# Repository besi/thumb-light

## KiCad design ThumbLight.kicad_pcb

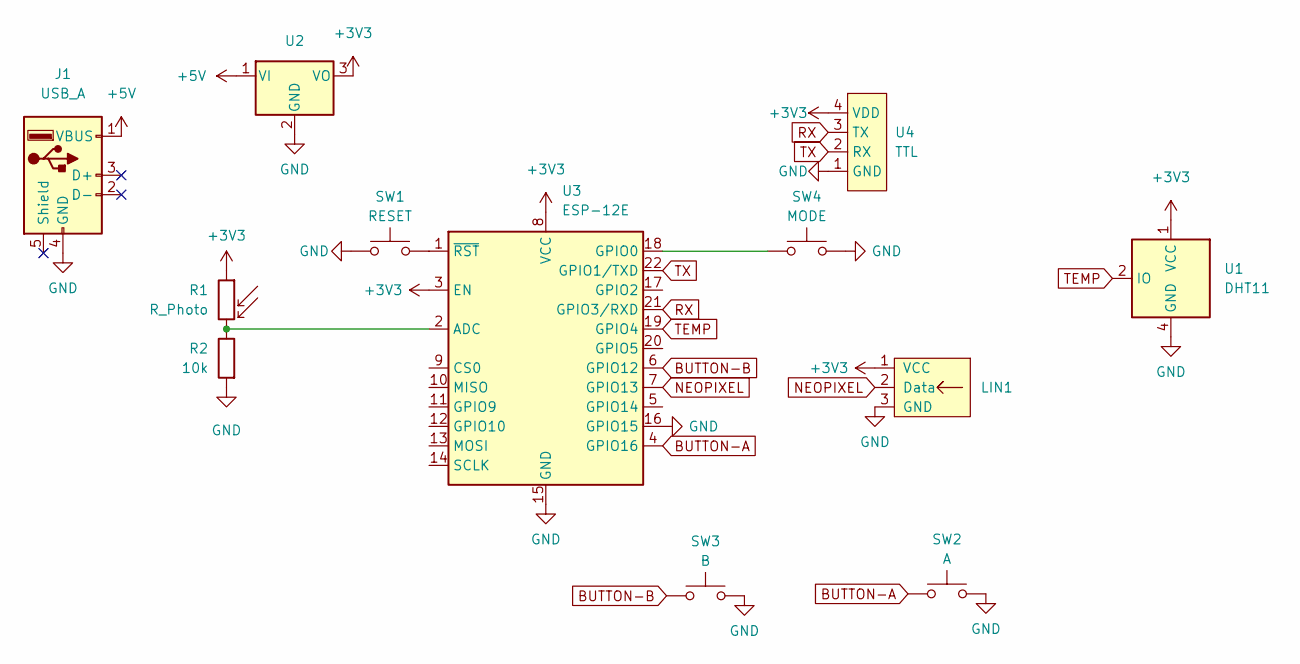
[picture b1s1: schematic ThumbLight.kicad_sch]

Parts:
J1: USB_A; usb-a-pcb
LIN1: LEDs_In; neopixel-strip
R1: R_Photo; R_LDR_5.0x4.1mm_P3mm_Vertical
R2: 10k; R_Axial_DIN0207_L6.3mm_D2.5mm_P7.62mm_Horizontal
SW1: RESET; SW_Push_1P1T_NO_Vertical_Wuerth_434133025816
SW2: A; SW_Push_1P1T_NO_Vertical_Wuerth_434133025816
SW3: B; SW_Push_1P1T_NO_Vertical_Wuerth_434133025816
SW4: MODE; SW_Push_1P1T_NO_Vertical_Wuerth_434133025816
U1: DHT11; Aosong_DHT11_5.5x12.0_P2.54mm
U2: UA78M33_TO252; TO-252-2
U3: ESP-12E
U4: TTL; PinHeader_1x04_P2.54mm_Vertical

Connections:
+3V3: LIN1.1 (VCC), R1.1, U1.1 (VCC), U2.3 (VO), U3.3 (EN), U3.8 (VCC), U4.4 (VDD)
+5V: J1.1 (VBUS), U2.1 (VI)
BUTTON-A: SW2.2, U3.4 (GPIO16)
BUTTON-B: SW3.2, U3.6 (GPIO12)
GND: J1.4 (GND), LIN1.3 (GND), R2.2, SW1.1, SW2.1, SW3.1, SW4.1, U1.4 (GND), U2.2 (GND), U3.15 (GND), U3.16 (GPIO15), U4.1 (GND)
NEOPIXEL: LIN1.2 (Data), U3.7 (GPIO13)
unnamed: SW1.2, U3.1 (~RST)
unnamed: SW4.2, U3.18 (GPIO0)
unnamed: R1.2, R2.1, U3.2 (ADC)
RX: U3.21 (GPIO3/RXD), U4.3 (TX)
TEMP: U1.2 (IO), U3.19 (GPIO4)
TX: U3.22 (GPIO1/TXD), U4.2 (RX)

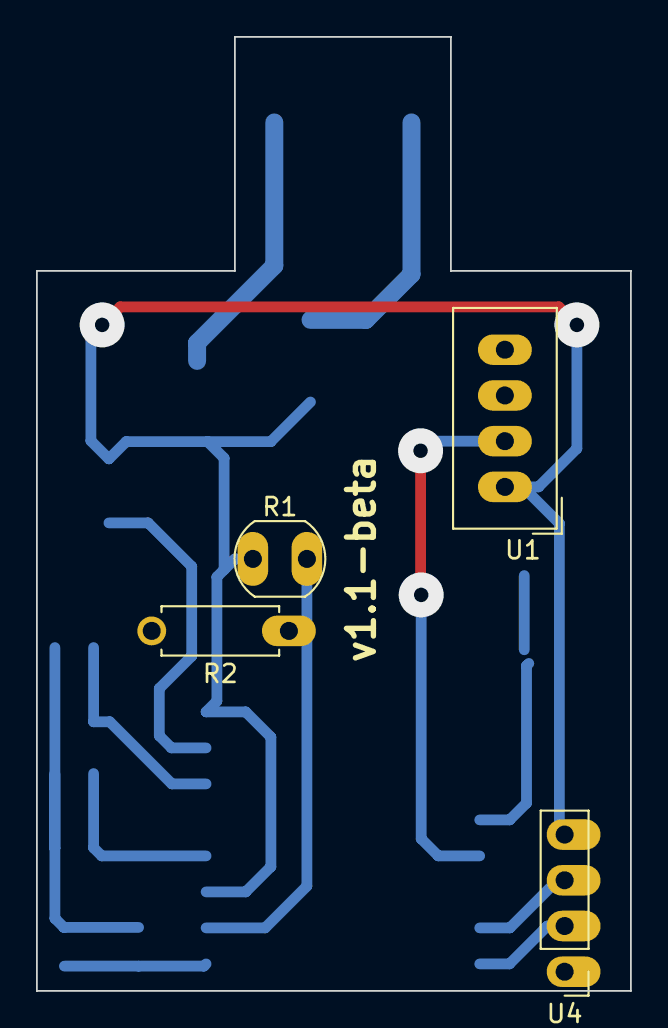
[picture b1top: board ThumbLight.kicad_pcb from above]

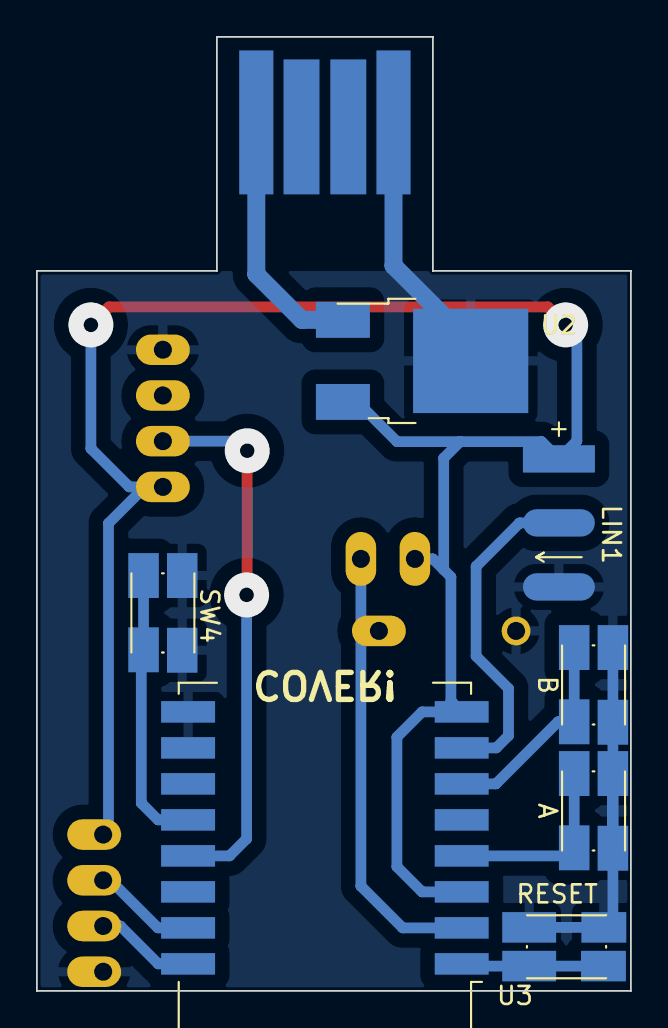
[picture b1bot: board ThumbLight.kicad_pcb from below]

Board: 2 copper layers, 33.0 x 53.0 mm, 12 parts (8 on the bottom side), 12 nets.

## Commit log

2023-11-24 Add TP4056 module
2023-11-24 Add FTDI component
2023-11-24 Add edges
2023-11-24 rough layout and remove battery functionality
2023-11-24 Add PROGRAM Jumper as well as a DHT11 sensor
2023-11-25 Add USB Footprint
2023-11-26 New basic layout
2023-11-26 Remove obsolete library
2023-11-26 Add neopixel strip
2023-11-26 Add buttons and light sensor
2023-11-26 Add Readme
2023-11-26 Silkscreen
2023-11-27 Prepare for plotting
2023-11-28 v1.1-beta improvements
2023-11-28 Elongate USB Plug
2023-11-28 Improvements over version 1.0
2023-11-28 Update USB library
2023-11-29 Initial software commit
2023-11-29 Add DHT11 demo code
2023-11-29 Update todos
2023-11-29 Update USB footprint
